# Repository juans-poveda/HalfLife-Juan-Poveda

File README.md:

# HalfLife-Juan-Poveda
Half life proyect 2026

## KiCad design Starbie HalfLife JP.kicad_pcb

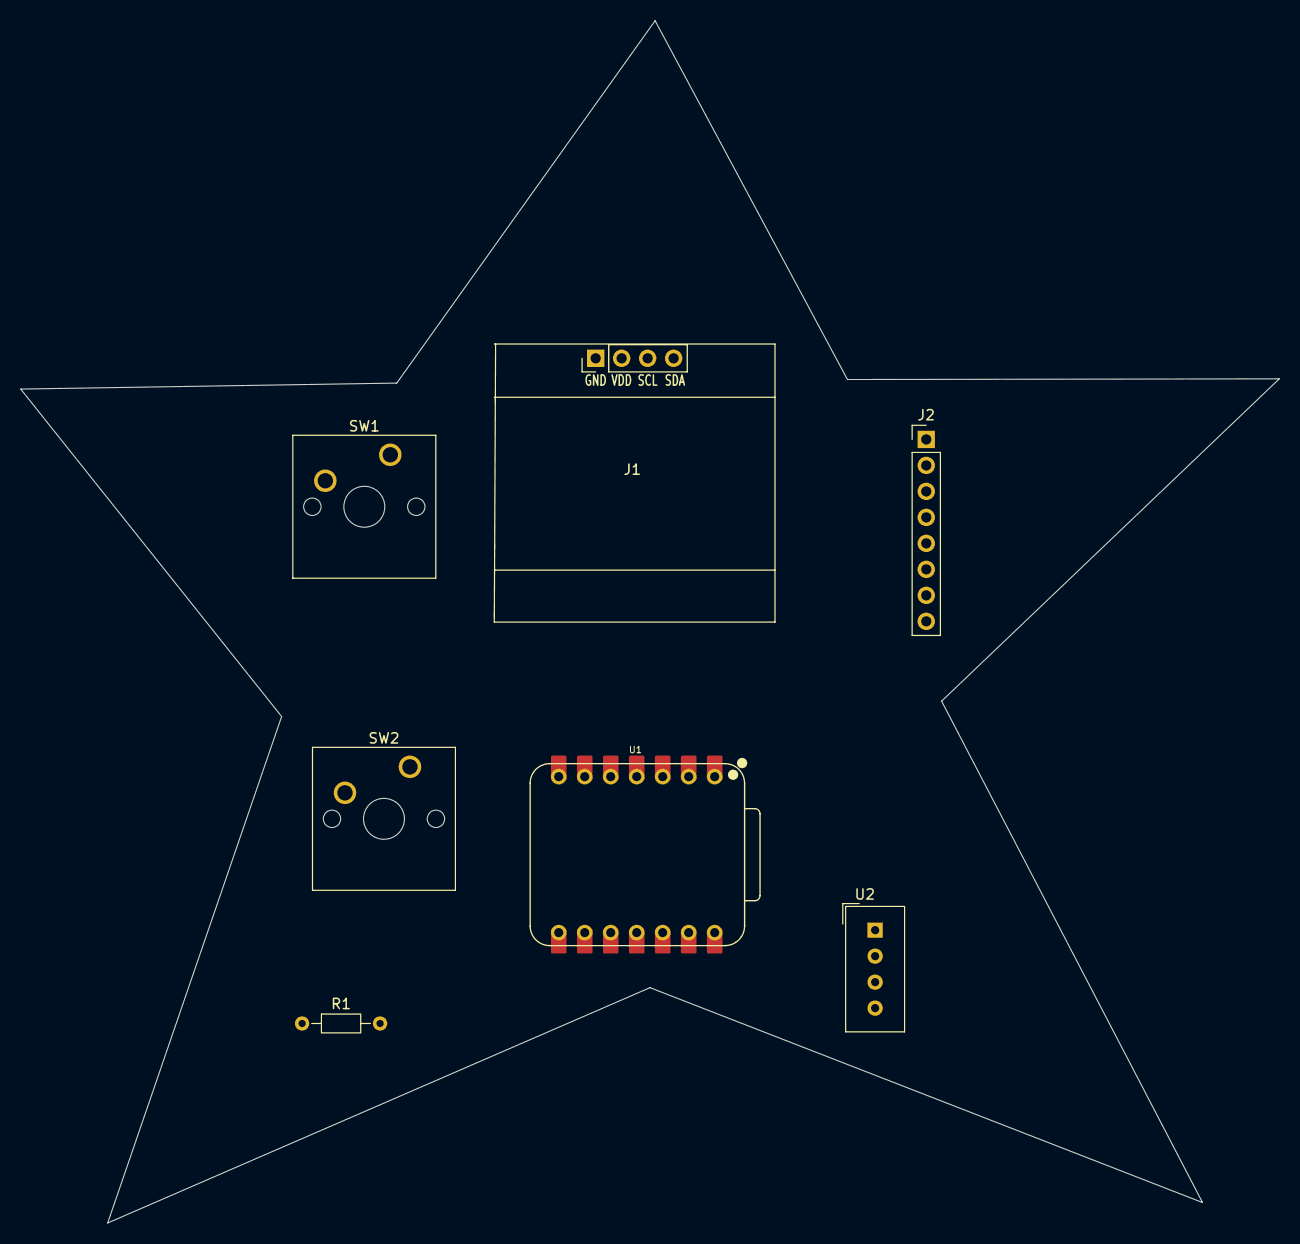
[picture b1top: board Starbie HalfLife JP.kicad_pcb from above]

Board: 2 copper layers, 123.0 x 117.5 mm, 7 parts (0 on the bottom side), 7 nets, no tracks yet.

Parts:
J1: Conn_01x04_Pin; Display_128x64_096_I2C
J2: Conn_01x08_Pin; PinHeader_1x08_P2.54mm_Vertical
R1: 10k; R_Axial_DIN0204_L3.6mm_D1.6mm_P7.62mm_Horizontal
SW1, SW2: SW_Push; SW_Cherry_MX_1.00u_PCB
U1: XIAO-ESP32-C3-SMD; XIAO-ESP32-C6-DIP
U2: DHT11; Aosong_DHT11_5.5x12.0_P2.54mm

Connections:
+3.3V: J1.4, J2.1, R1.1, U1.12 (3V3_OUT), U2.1 (VDD)
/DHT11 DATA: R1.2, U1.2 (D1), U2.2 (DATA)
/GPI02: SW1.1, U1.3 (D2)
/GPI03: SW2.1, U1.4 (D3)
/SCL: J1.2, J2.3, U1.5 (D4)
/SDA: J1.3, J2.4, U1.6 (D5)
GND: J1.1, J2.2, SW1.2, SW2.2, U1.13 (GND), U2.4 (GND)
